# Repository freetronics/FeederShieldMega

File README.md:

Feeder Shield Mega
==================
Copyright 2018-2020 Freetronics Pty Ltd  www.freetronics.com  

Pick and place feeder controller for DIY feeders. Compatible with the
0816 feeders designed by MGRL:

  https://docs.mgrl.de/maschine:pickandplace:feeder:0816feeder

These feeders are commonly used with DIY pick and place machines
running OpenPNP:

  http://openpnp.org

Run the MGRL feeder control firmware.

Adds an I2C display that can be used for reporting events and part
counts.

Uses 10-way IDC cables to connect batches of 4 feeders. Mates to the
MGRL0816 Feeder Link board, which bridges across the 4-pin connections
on 4 feeders mounted side by side.

Features:

 * 24 feeder outputs
 * PWM output and feedback input
 * GND and 5V supply to feeders
 * Software controlled feeder power
 * 128x32 OLED

You can view more online at:

  http://www.freetronics.com.au/fsm

INSTALLATION
------------
The design is saved as an EAGLE project. EAGLE PCB design software is
available from www.cadsoftusa.com free for non-commercial use. To use
this project download it and place the directory containing these files
into the "eagle" directory on your computer. Then open EAGLE and
navigate to the project.

DISTRIBUTION
------------
The specific terms of distribution of this project are governed by the
license referenced below.

LICENSE
-------
Licensed under the TAPR Open Hardware License (www.tapr.org/OHL).
The "license" folder within this repository also contains a copy of
this license in plain text format.

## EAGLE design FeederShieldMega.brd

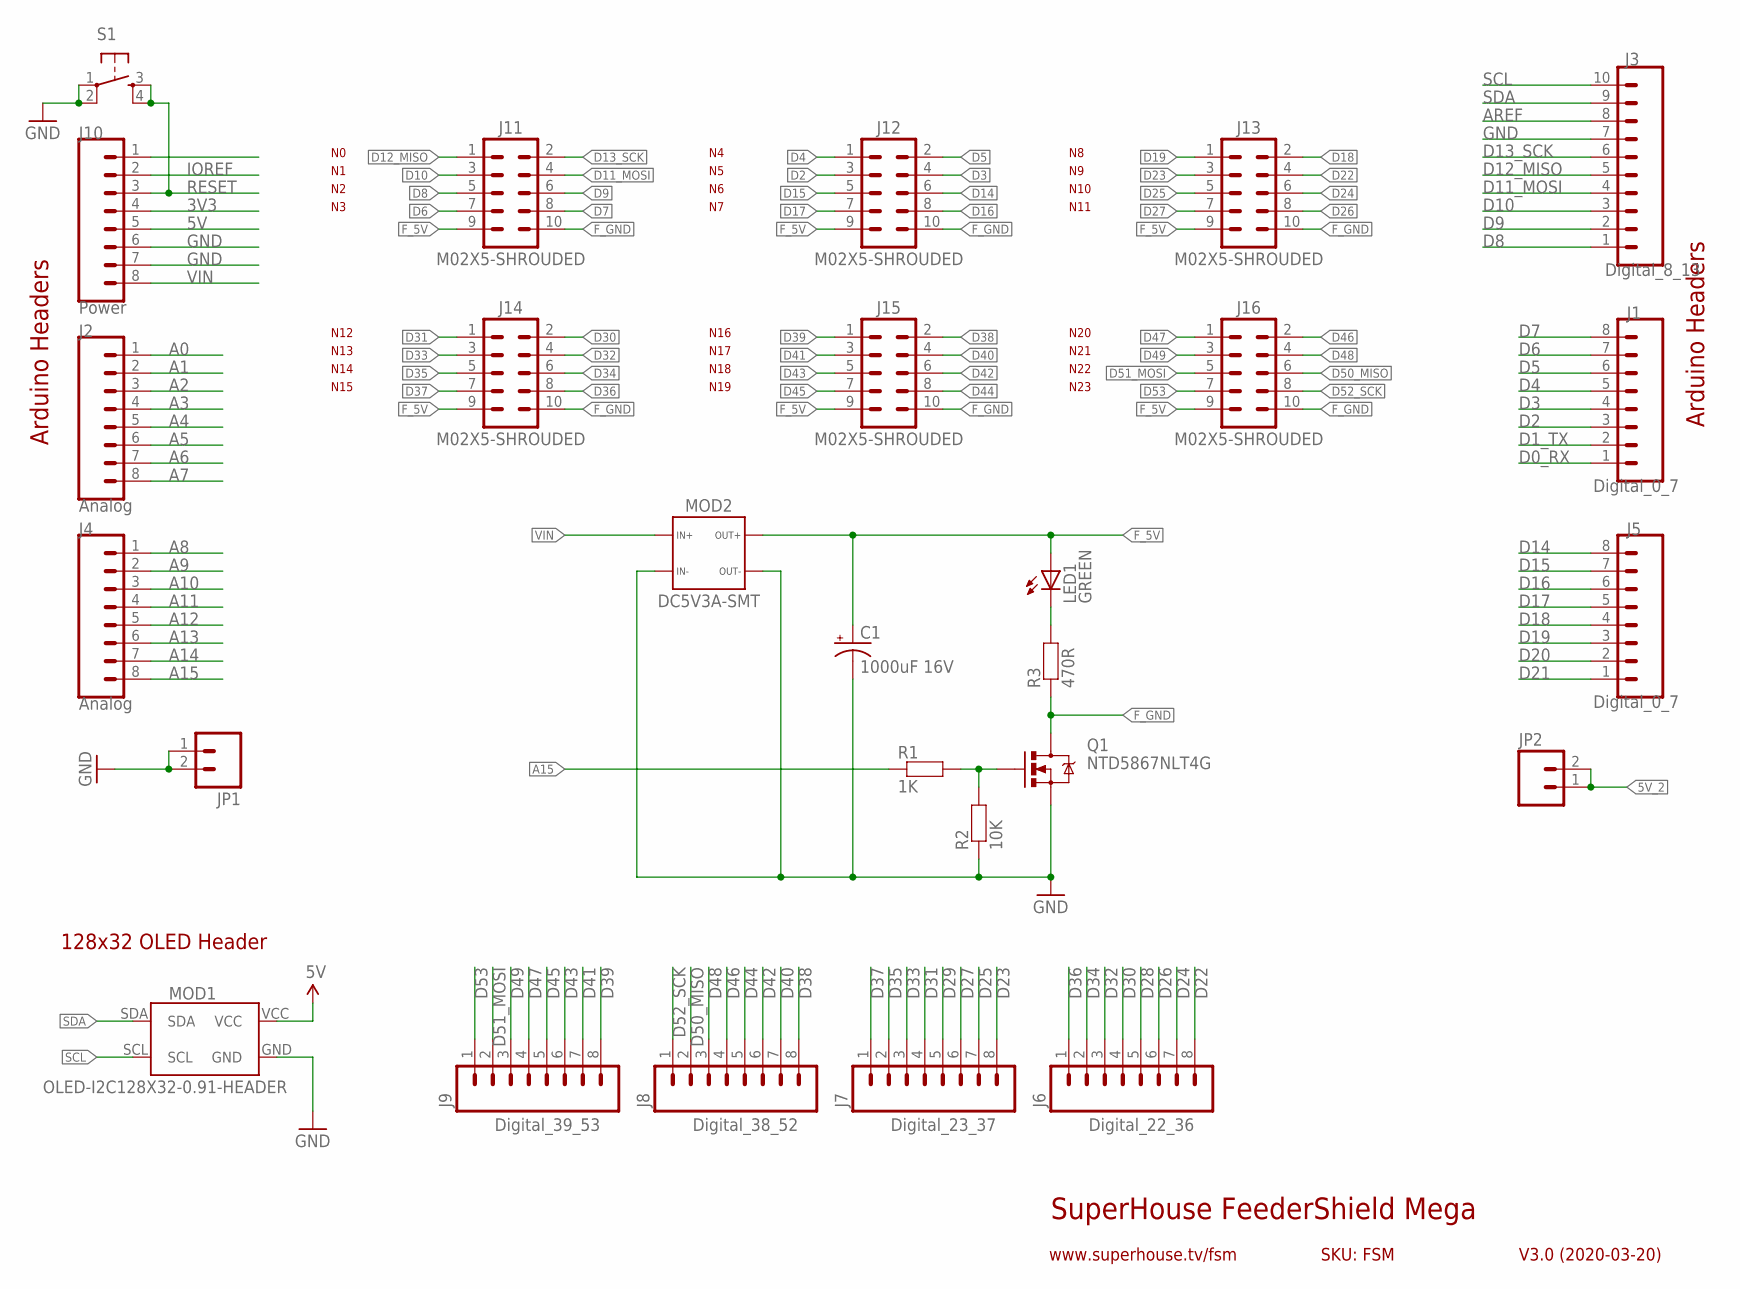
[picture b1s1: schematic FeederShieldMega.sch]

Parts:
C1: 1000uF 16V; CPOL-RADIAL-5.08-10X18-FLAT
J1, J5: Digital_0_7; 1X08-P-BELOW
J2, J4: Analog; 1X08-P-BELOW
J3: Digital_8_13; 1X10-P-BELOW
J6: Digital_22_36; 1X08-P-BELOW
J7: Digital_23_37; 1X08-P-BELOW
J8: Digital_38_52; 1X08-P-BELOW
J9: Digital_39_53; 1X08-P-BELOW
J10: Power; 1X08-P-BELOW
J11, J12, J13, J14, J15, J16: M02X5-SHROUDED; 2X05-2.54-SHROUDED
JP1, JP2: M02-PIN-BELOW; 1X02-P-BELOW
LED1: GREEN; LED-0603
MOD1: OLED-I2C128X32-0.91-HEADER; OLED-128X32-0.91-HEADER
MOD2: DC5V3A-SMT
Q1: NTD5867NLT4G; DPACK
R1: 1K; R0603
R2: 10K; R0603
R3: 470R; R0603
S1: TAC_SWITCH-PTH-6; TACTILE-PTH-6MM

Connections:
3V3: J10.4
5V: J10.5, MOD1.VCC
5V_2: JP2.1, JP2.2
A0: J2.1
A1: J2.2
A2: J2.3
A3: J2.4
A4: J2.5
A5: J2.6
A6: J2.7
A7: J2.8
A8: J4.1
A9: J4.2
A10: J4.3
A11: J4.4
A12: J4.5
A13: J4.6
A14: J4.7
A15: J4.8, R1.1
AREF: J3.8
D0_RX: J1.1
D1_TX: J1.2
D2: J1.3, J12.3
D3: J1.4, J12.4
D4: J1.5, J12.1
D5: J1.6, J12.2
D6: J1.7, J11.7
D7: J1.8, J11.8
D8: J3.1, J11.5
D9: J3.2, J11.6
D10: J3.3, J11.3
D11_MOSI: J3.4, J11.4
D12_MISO: J3.5, J11.1
D13_SCK: J3.6, J11.2
D14: J5.8, J12.6
D15: J5.7, J12.5
D16: J5.6, J12.8
D17: J5.5, J12.7
D18: J5.4, J13.2
D19: J5.3, J13.1
D20: J5.2
D21: J5.1
D22: J6.8, J13.4
D23: J7.8, J13.3
D24: J6.7, J13.6
D25: J7.7, J13.5
D26: J6.6, J13.8
D27: J7.6, J13.7
D28: J6.5
D29: J7.5
D30: J6.4, J14.2
D31: J7.4, J14.1
D32: J6.3, J14.4
D33: J7.3, J14.3
D34: J6.2, J14.6
D35: J7.2, J14.5
D36: J6.1, J14.8
D37: J7.1, J14.7
D38: J8.8, J15.2
D39: J9.8, J15.1
D40: J8.7, J15.4
D41: J9.7, J15.3
D42: J8.6, J15.6
D43: J9.6, J15.5
D44: J8.5, J15.8
D45: J9.5, J15.7
D46: J8.4, J16.2
D47: J9.4, J16.1
D48: J8.3, J16.4
D49: J9.3, J16.3
D50_MISO: J8.2, J16.6
D51_MOSI: J9.2, J16.5
D52_SCK: J8.1, J16.8
D53: J9.1, J16.7
F_5V: C1.1 (+), J11.9, J12.9, J13.9, J14.9, J15.9, J16.9, LED1.A, MOD2.3A (3), MOD2.3B (3)
F_GND: J11.10, J12.10, J13.10, J14.10, J15.10, J16.10, Q1.2 (D), R3.1
GND: C1.2 (-), J3.7, J10.6, J10.7, JP1.1, JP1.2, MOD1.GND, MOD2.1A (1), MOD2.1B (1), MOD2.4A (4), MOD2.4B (4), Q1.3 (S), R2.1, S1.1, S1.2
IOREF: J10.2
unnamed: Q1.1 (G), R1.2, R2.2
unnamed: LED1.C, R3.2
RESET: J10.3, S1.3, S1.4
SCL: J3.10, MOD1.SCL
SDA: J3.9, MOD1.SDA
VIN: J10.8, MOD2.2A (2), MOD2.2B (2)

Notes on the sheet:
SuperHouse FeederShield Mega
V3.0 (2020-03-20)
www.superhouse.tv/fsm
SKU: FSM
Arduino Headers
128x32 OLED Header
N10
N11
N12
N13
N14
N15
N16
N17
N18
N19
N20
N21
N22
N23

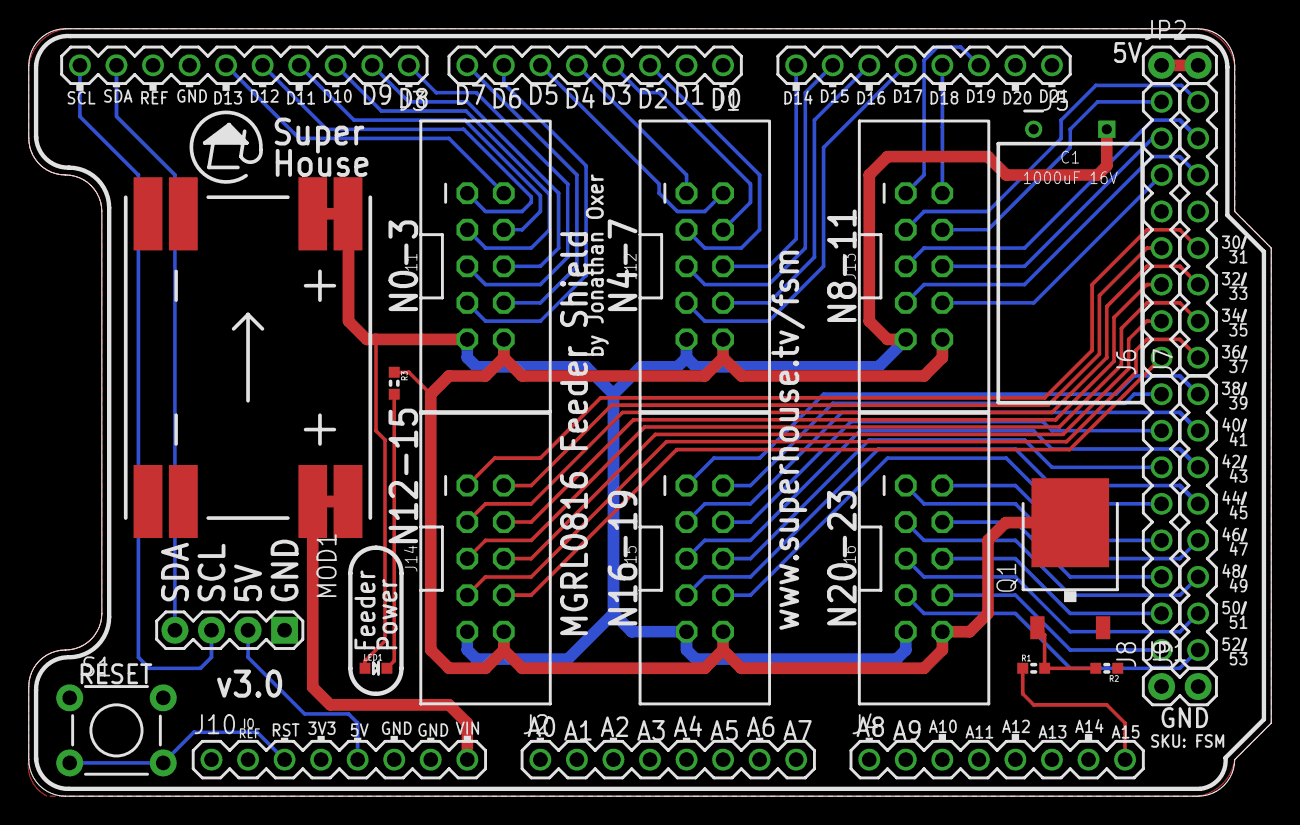
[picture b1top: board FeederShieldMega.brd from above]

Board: 2 copper layers, 86.4 x 53.3 mm, 27 parts (0 on the bottom side), 60 nets.

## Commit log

2018-07-12 Initial layout
2018-07-12 Tweaks for v1.0 release
2018-07-12 Added readme and license
2018-07-12 DRC for release v1.0
2020-01-27 Major rework to use 10-way IDC connections for v2.0 release
2020-04-30 Added 5V 3A voltage regulator and removed 2 bulk decoupling caps for v3.0 release

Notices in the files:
FeederShieldMega.brd:
Copyright 2018-2020 SuperHouse Automation
Open Hardware License:
www.tapr.org/OHL
